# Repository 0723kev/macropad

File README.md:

# Kev's Macropad - The Hybrid Macropad

This is my custom 10-key (8 MX, 2 encoder) mechanical macropad that has dual rotary encoders, per-key RGB lighting, and an OLED status screen. 
It is powered by the XIAO RP2040 and an MCP23008 I/O expander to make sure that I can do as much as I can on this board with such a small footprint.

## Images

### Schematic

### PCB

### Assembly

### Exploded Assembly

## Firmware
Firmware made using KMK

## BOM
> **`*`** denotes a part not included in the hackpad kit. I will supply them.

| **Part**  | **Qty** | **Description**                    | **Remarks**            |
|-----------|---------|------------------------------------|------------------------|
| MCU       | 1       | Xiao RP2040                        |                        |
| Expander  | 1       | MCP23008                           | *                      |
| Switches  | 8       | MX-style CLEAR mechanical switches |                        |
| Keycaps   | 8       | DSA or XDA Profile (1u)            |                        |
| Display   | 1       | 0.91" OLED 12C                     | Pinout GND-VCC-SDL-SDA |
| LEDs      | 8       | SK6812 MINI-E                      | Reverse-mount          |
| Resistors | 2       | 2.2kΩ or 4.7kΩ                     | * I2C Pull-ups         |
| Diodes    | 10      | 1N4148                             | Through-hole           |
| Hardware  | 4       | M3 x 16mm Screws                   | Case                   |
| Hardware  | 4       | M3 Heatset Inserts                 | 5mm x 4mm              |

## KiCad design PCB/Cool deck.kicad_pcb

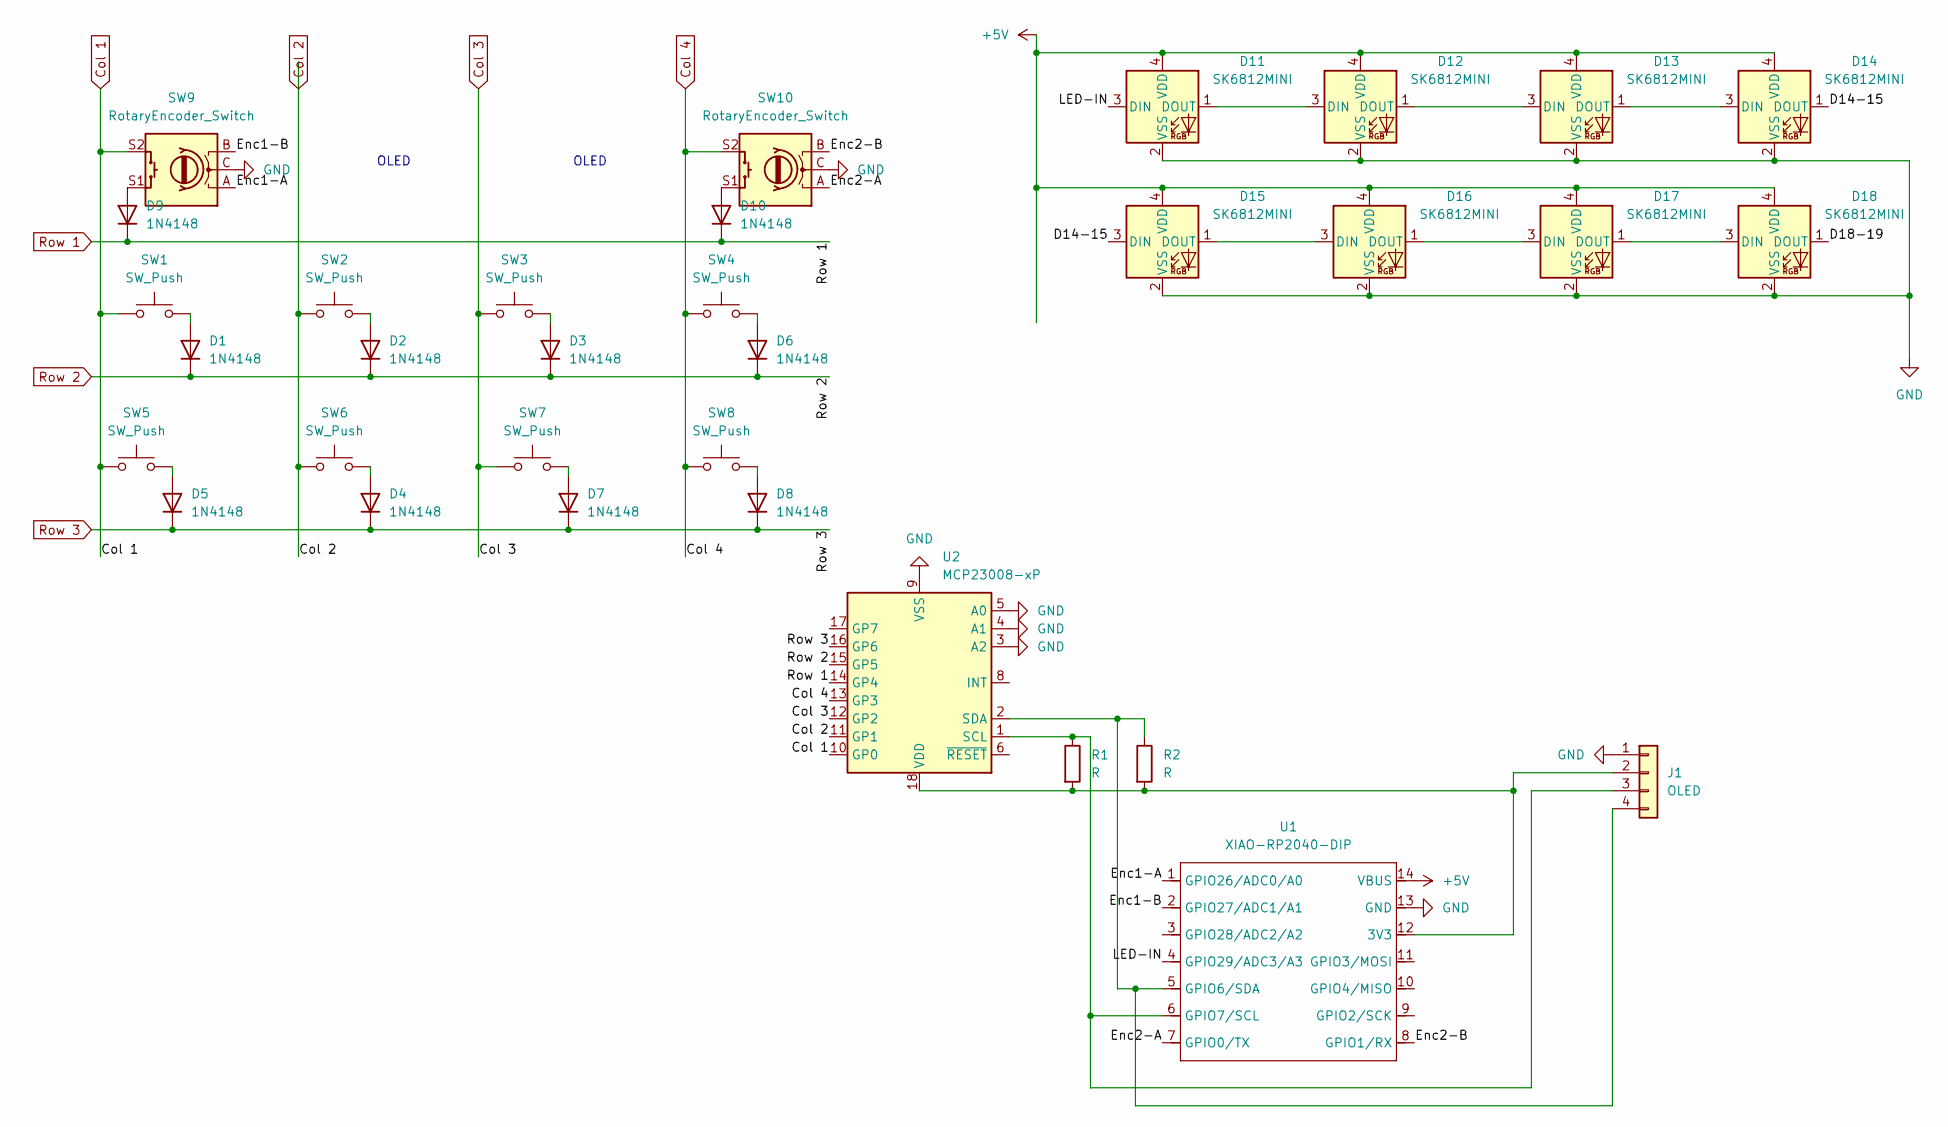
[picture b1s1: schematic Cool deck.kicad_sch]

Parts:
D1, D2, D3, D4, D5, D6, D7, D8, D9, D10: 1N4148; D_DO-35_SOD27_P7.62mm_Horizontal; LCSC C84410
D11, D12, D13, D14, D15, D16, D17, D18: SK6812MINI; LED_SK6812-E; LCSC C5149201
J1: OLED; SSD1306-0.91-OLED-4pin-128x32
R1, R2: R; R_Axial_DIN0207_L6.3mm_D2.5mm_P7.62mm_Horizontal; LCSC C20560790
SW1, SW2, SW3, SW4, SW5, SW6, SW7, SW8: SW_Push; SW_Cherry_MX_1.00u_PCB
SW9, SW10: RotaryEncoder_Switch; RotaryEncoder_Alps_EC11E-Switch_Vertical_H20mm; LCSC C202365
U1: XIAO-RP2040-DIP; LCSC C9900176459
U2: MCP23008-xP; DIP-18_W7.62mm; LCSC C646745

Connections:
+5V: D11.4 (VDD), D12.4 (VDD), D13.4 (VDD), D14.4 (VDD), D15.4 (VDD), D16.4 (VDD), D17.4 (VDD), D18.4 (VDD), U1.14 (VBUS)
/D14-15: D14.1 (DOUT), D15.3 (DIN)
/D18-19: D18.1 (DOUT)
/Enc1-A: SW9.A, U1.1 (GPIO26/ADC0/A0)
/Enc1-B: SW9.B, U1.2 (GPIO27/ADC1/A1)
/Enc2-A: SW10.A, U1.7 (GPIO0/TX)
/Enc2-B: SW10.B, U1.8 (GPIO1/RX)
/LED-IN: D11.3 (DIN), U1.4 (GPIO29/ADC3/A3)
Col 1: SW1.1, SW5.1, SW9.S2, U2.10 (GP0)
Col 2: SW2.1, SW6.1, U2.11 (GP1)
Col 3: SW3.1, SW7.1, U2.12 (GP2)
Col 4: SW4.1, SW8.1, SW10.S2, U2.13 (GP3)
GND: D11.2 (VSS), D12.2 (VSS), D13.2 (VSS), D14.2 (VSS), D15.2 (VSS), D16.2 (VSS), D17.2 (VSS), D18.2 (VSS), J1.1, SW9.C, SW10.C, U1.13 (GND), U2.3 (A2), U2.4 (A1), U2.5 (A0), U2.9 (VSS)
unnamed: D1.2 (A), SW1.2
unnamed: D2.2 (A), SW2.2
unnamed: D3.2 (A), SW3.2
unnamed: D4.2 (A), SW6.2
unnamed: D5.2 (A), SW5.2
unnamed: D6.2 (A), SW4.2
unnamed: D7.2 (A), SW7.2
unnamed: D8.2 (A), SW8.2
unnamed: D9.2 (A), SW9.S1
unnamed: D10.2 (A), SW10.S1
unnamed: D11.1 (DOUT), D12.3 (DIN)
unnamed: D12.1 (DOUT), D13.3 (DIN)
unnamed: D13.1 (DOUT), D14.3 (DIN)
unnamed: D15.1 (DOUT), D16.3 (DIN)
unnamed: D16.1 (DOUT), D17.3 (DIN)
unnamed: D17.1 (DOUT), D18.3 (DIN)
unnamed: J1.2, R1.2, R2.2, U1.12 (3V3), U2.18 (VDD)
unnamed: J1.3, R1.1, U1.6 (GPIO7/SCL), U2.1 (SCL)
unnamed: J1.4, R2.1, U1.5 (GPIO6/SDA), U2.2 (SDA)
Row 1: D9.1 (K), D10.1 (K), U2.14 (GP4)
Row 2: D1.1 (K), D2.1 (K), D3.1 (K), D6.1 (K), U2.15 (GP5)
Row 3: D4.1 (K), D5.1 (K), D7.1 (K), D8.1 (K), U2.16 (GP6)

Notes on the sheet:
OLED

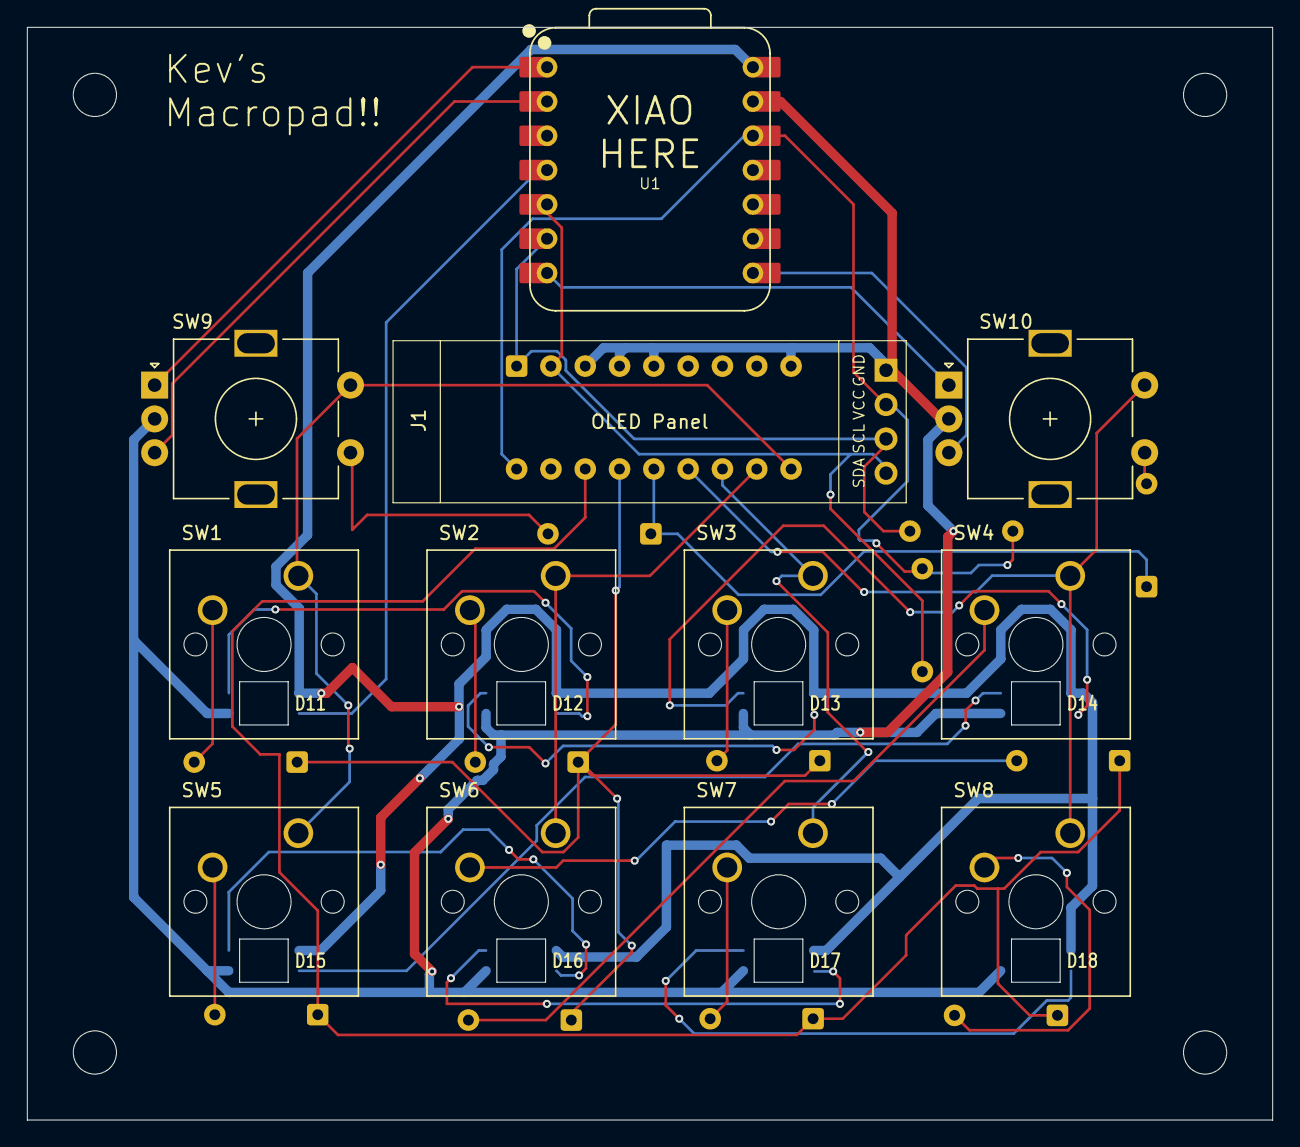
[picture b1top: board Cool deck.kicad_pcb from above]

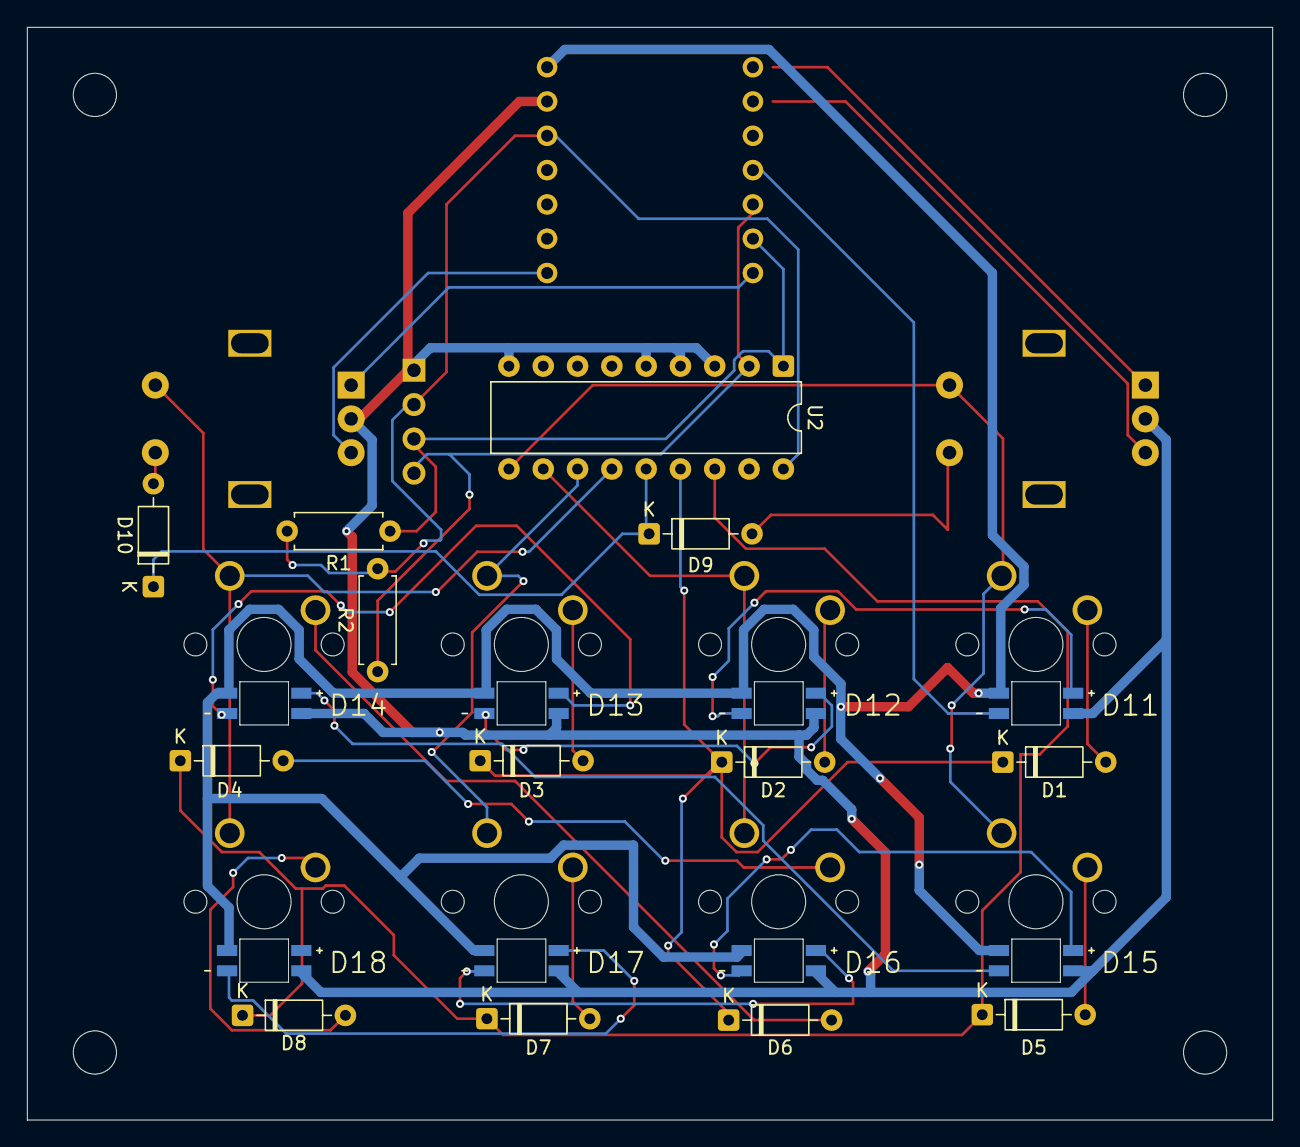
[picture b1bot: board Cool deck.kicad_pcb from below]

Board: 2 copper layers, 92.2 x 80.9 mm, 33 parts (21 on the bottom side), 34 nets.

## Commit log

2025-12-29 start populating data
2025-12-29 start readme, add cad files, add kicad files
2025-12-29 start firmware
2025-12-29 add libs
2025-12-29 add final images
2025-12-29 Create LICENSE
